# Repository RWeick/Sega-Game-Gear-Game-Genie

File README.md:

# Sega-Game-Gear-Game-Genie
The Kicad files and EPROM dump of the Sega Game Gear Game Genie.

The EPROM and PLD used were made by iMP, and I can't find a ton out there about them.

PCB Thicknesses: 0.8 mm

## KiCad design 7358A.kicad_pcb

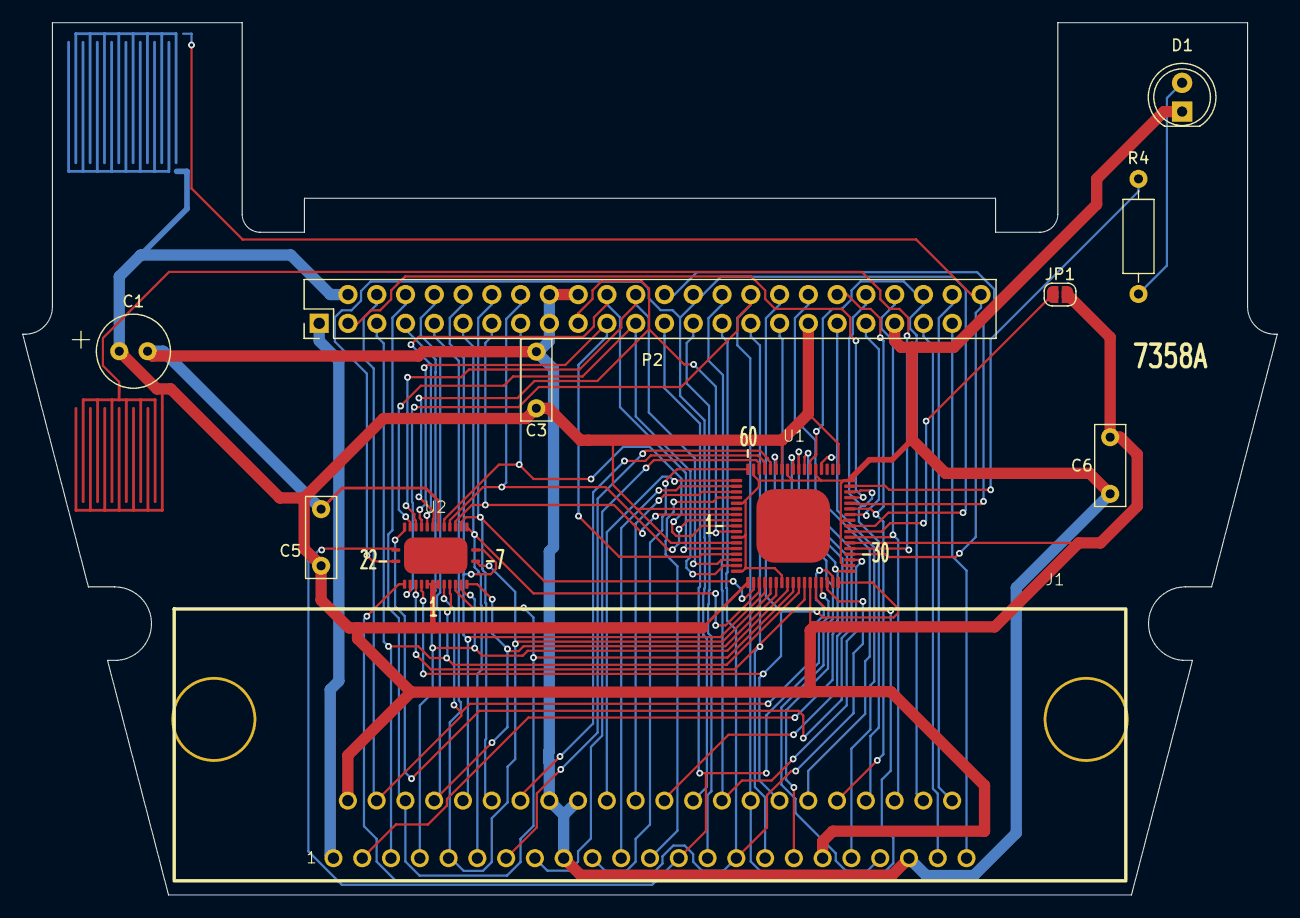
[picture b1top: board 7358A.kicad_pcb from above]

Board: 2 copper layers, 110.8 x 77.0 mm, 13 parts (1 on the bottom side), 58 nets.

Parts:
C1: C_Polarized; C_Radial_D6.3mm_H5.0mm_P2.50mm
C3, C5, C6: C_Small; C_Disc_D7.0mm_W2.5mm_P5.00mm
D1: LED; LED_D5.0mm
J1: Game Cartridge Connector; Cartridge Slot
JP1: Jumper_2_Bridged; SolderJumper-2_P1.3mm_Open_RoundedPad1.0x1.5mm
P2: System Edge Connector; PinHeader_2x24_P2.54mm_Vertical
R4: 1.2K Ohm 5%; R_Axial_DIN0207_L6.3mm_D2.5mm_P10.16mm_Horizontal
SW1: Bottom Button; 12 Prong Button Pad
SW2: Top Button; 16 Prong Button Pad
U1: iMP PLD
U2: iMP EPROM

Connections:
/+34V: J1.1 (+34V), P2.1
/A0: J1.12 (A0), P2.12, U1.11 (A0), U2.10 (A0)
/A1: J1.11 (A1), P2.11, U1.12 (A1), U2.9 (A1)
/A2: J1.10 (A2), P2.10, U1.13 (A2), U2.8 (A2)
/A3: J1.9 (A3), P2.9, U1.14 (A3), U2.7 (A3)
/A4: J1.8 (A4), P2.8, U1.15 (A4), U2.6 (A4)
/A5: J1.7 (A5), P2.7, U1.17 (A5), U2.5 (A5)
/A6: J1.6 (A6), P2.6, U1.18 (A6), U2.4 (A6)
/A7: J1.5 (A7), P2.5, U1.19 (A7), U2.3 (A7)
/A8: J1.31 (A8), P2.31, U1.20 (A8), U2.25 (A8)
/A9: J1.30 (A9), P2.30, U1.22 (A9), U2.24 (A9)
/A10: J1.25 (A10), P2.25, U1.23 (A10), U2.21 (A10)
/A11: J1.29 (A11), P2.29, U1.24 (A11), U2.23 (A11)
/A12: J1.4 (A12), P2.4, U1.25 (A12), U2.2 (A12)
/A13: J1.32 (A13), P2.32, U1.26 (A13), U2.26 (A13)
/A14: J1.33 (A14), P2.33, U1.27 (A14)
/A15: J1.28 (A15), P2.28, U1.29 (A15)
/Bottom.Button: SW1.1, U1.31 (Bottom.Button)
/Clock: J1.40 (Clock), P2.40, U1.33 (Clock)
/D0.Game: J1.13 (D0), U1.56 (D0.Game)
/D0.Sys: P2.13, U1.67 (D0.Sys), U2.11 (D0)
/D1.Game: J1.14 (D1), U1.57 (D1.Game)
/D1.Sys: P2.14, U1.68 (D1.Sys), U2.12 (D1)
/D2.Game: J1.15 (D2), U1.58 (D2.Game)
/D2.Sys: P2.15, U1.1 (D2.Sys), U2.13 (D2)
/D3.Game: J1.19 (D3), U1.60 (D3.Game)
/D3.Sys: P2.19, U1.2 (D3.Sys), U2.15 (D3)
/D4.Game: J1.20 (D4), U1.61 (D4.Game)
/D4.Sys: P2.20, U1.5 (D4.Sys), U2.16 (D4)
/D5.Game: J1.21 (D5), U1.62 (D5.Game)
/D5.Sys: P2.21, U1.6 (D5.Sys), U2.17 (D5)
/D6.Game: J1.22 (D6), U1.63 (D6.Game)
/D6.Sys: P2.22, U1.7 (D6.Sys), U2.18 (D6)
/D7.Game: J1.23 (D7), U1.64 (D7.Game)
/D7.Sys: P2.23, U1.8 (D7.Sys), U2.19 (D7)
/GND: C1.2, C3.2, C5.2, C6.1, D1.1 (K), J1.16 (GND), J1.17 (GND), J1.18 (GND), J1.41 (GND), P2.16, P2.17, P2.18, P2.41, U1.3 (GND), U1.9 (GND), U1.16 (GND), U1.28 (GND), U1.36 (GND), U1.43 (GND), U1.48 (GND), U1.53 (GND), U1.59 (GND), U1.65 (GND), U2.14 (GND)
/Jmp.VCC: JP1.1 (A), U1.34 (VCC)
/LED: R4.2, U1.42 (LED)
/TV_L: J1.45 (TV_L), P2.45
/TV_R: J1.44 (TV_R), P2.44
/Top.Button: P2.46, SW2.1, U1.30 (Top.Button)
/VCC: C1.1, C3.1, C5.1, C6.2, J1.2 (+5V), J1.35 (+5V), JP1.2 (B), P2.2, P2.35, SW1.2, SW2.2, U1.4 (VCC), U1.10 (VCC), U1.21 (VCC), U1.32 (VCC), U1.44 (VCC), U1.54 (VCC), U1.66 (VCC), U2.1 (VCC)
/~CE.Game: J1.24 (~CE), U1.51 (~CE.Game)
/~CE.Sys: P2.24, U1.39 (~CE.Sys)
/~EPROM.CE: U1.50 (~EPROM.CE), U2.20 (~CE)
/~GG: J1.42 (~GG), P2.42, U1.49 (~GG)
/~IOReq: J1.37 (~IOReq), P2.37, U1.47 (~IO_REQ)
/~M0-7: J1.27 (~M0-7), P2.27
/~M1: J1.36 (~M1), P2.36, U1.38 (~M1)
/~M8-B: J1.34 (~M8-B), P2.34
/~Read: J1.26 (~Read), P2.26, U1.35 (~Read), U2.22 (~OE)
/~Refresh: J1.38 (~Refresh), P2.38, U1.41 (~Refresh)
/~Reset.Game: J1.39 (~Reset), U1.55 (~Reset.Game)
/~Reset.Sys: P2.39, U1.37 (~Reset.Sys)
/~TV: J1.43 (~TV), P2.43
/~Write.Game: J1.3 (~Write), U1.52 (~Write.Game)
/~Write.Sys: P2.3, U1.40 (~Write.Sys)
unnamed: D1.2 (A), R4.1
